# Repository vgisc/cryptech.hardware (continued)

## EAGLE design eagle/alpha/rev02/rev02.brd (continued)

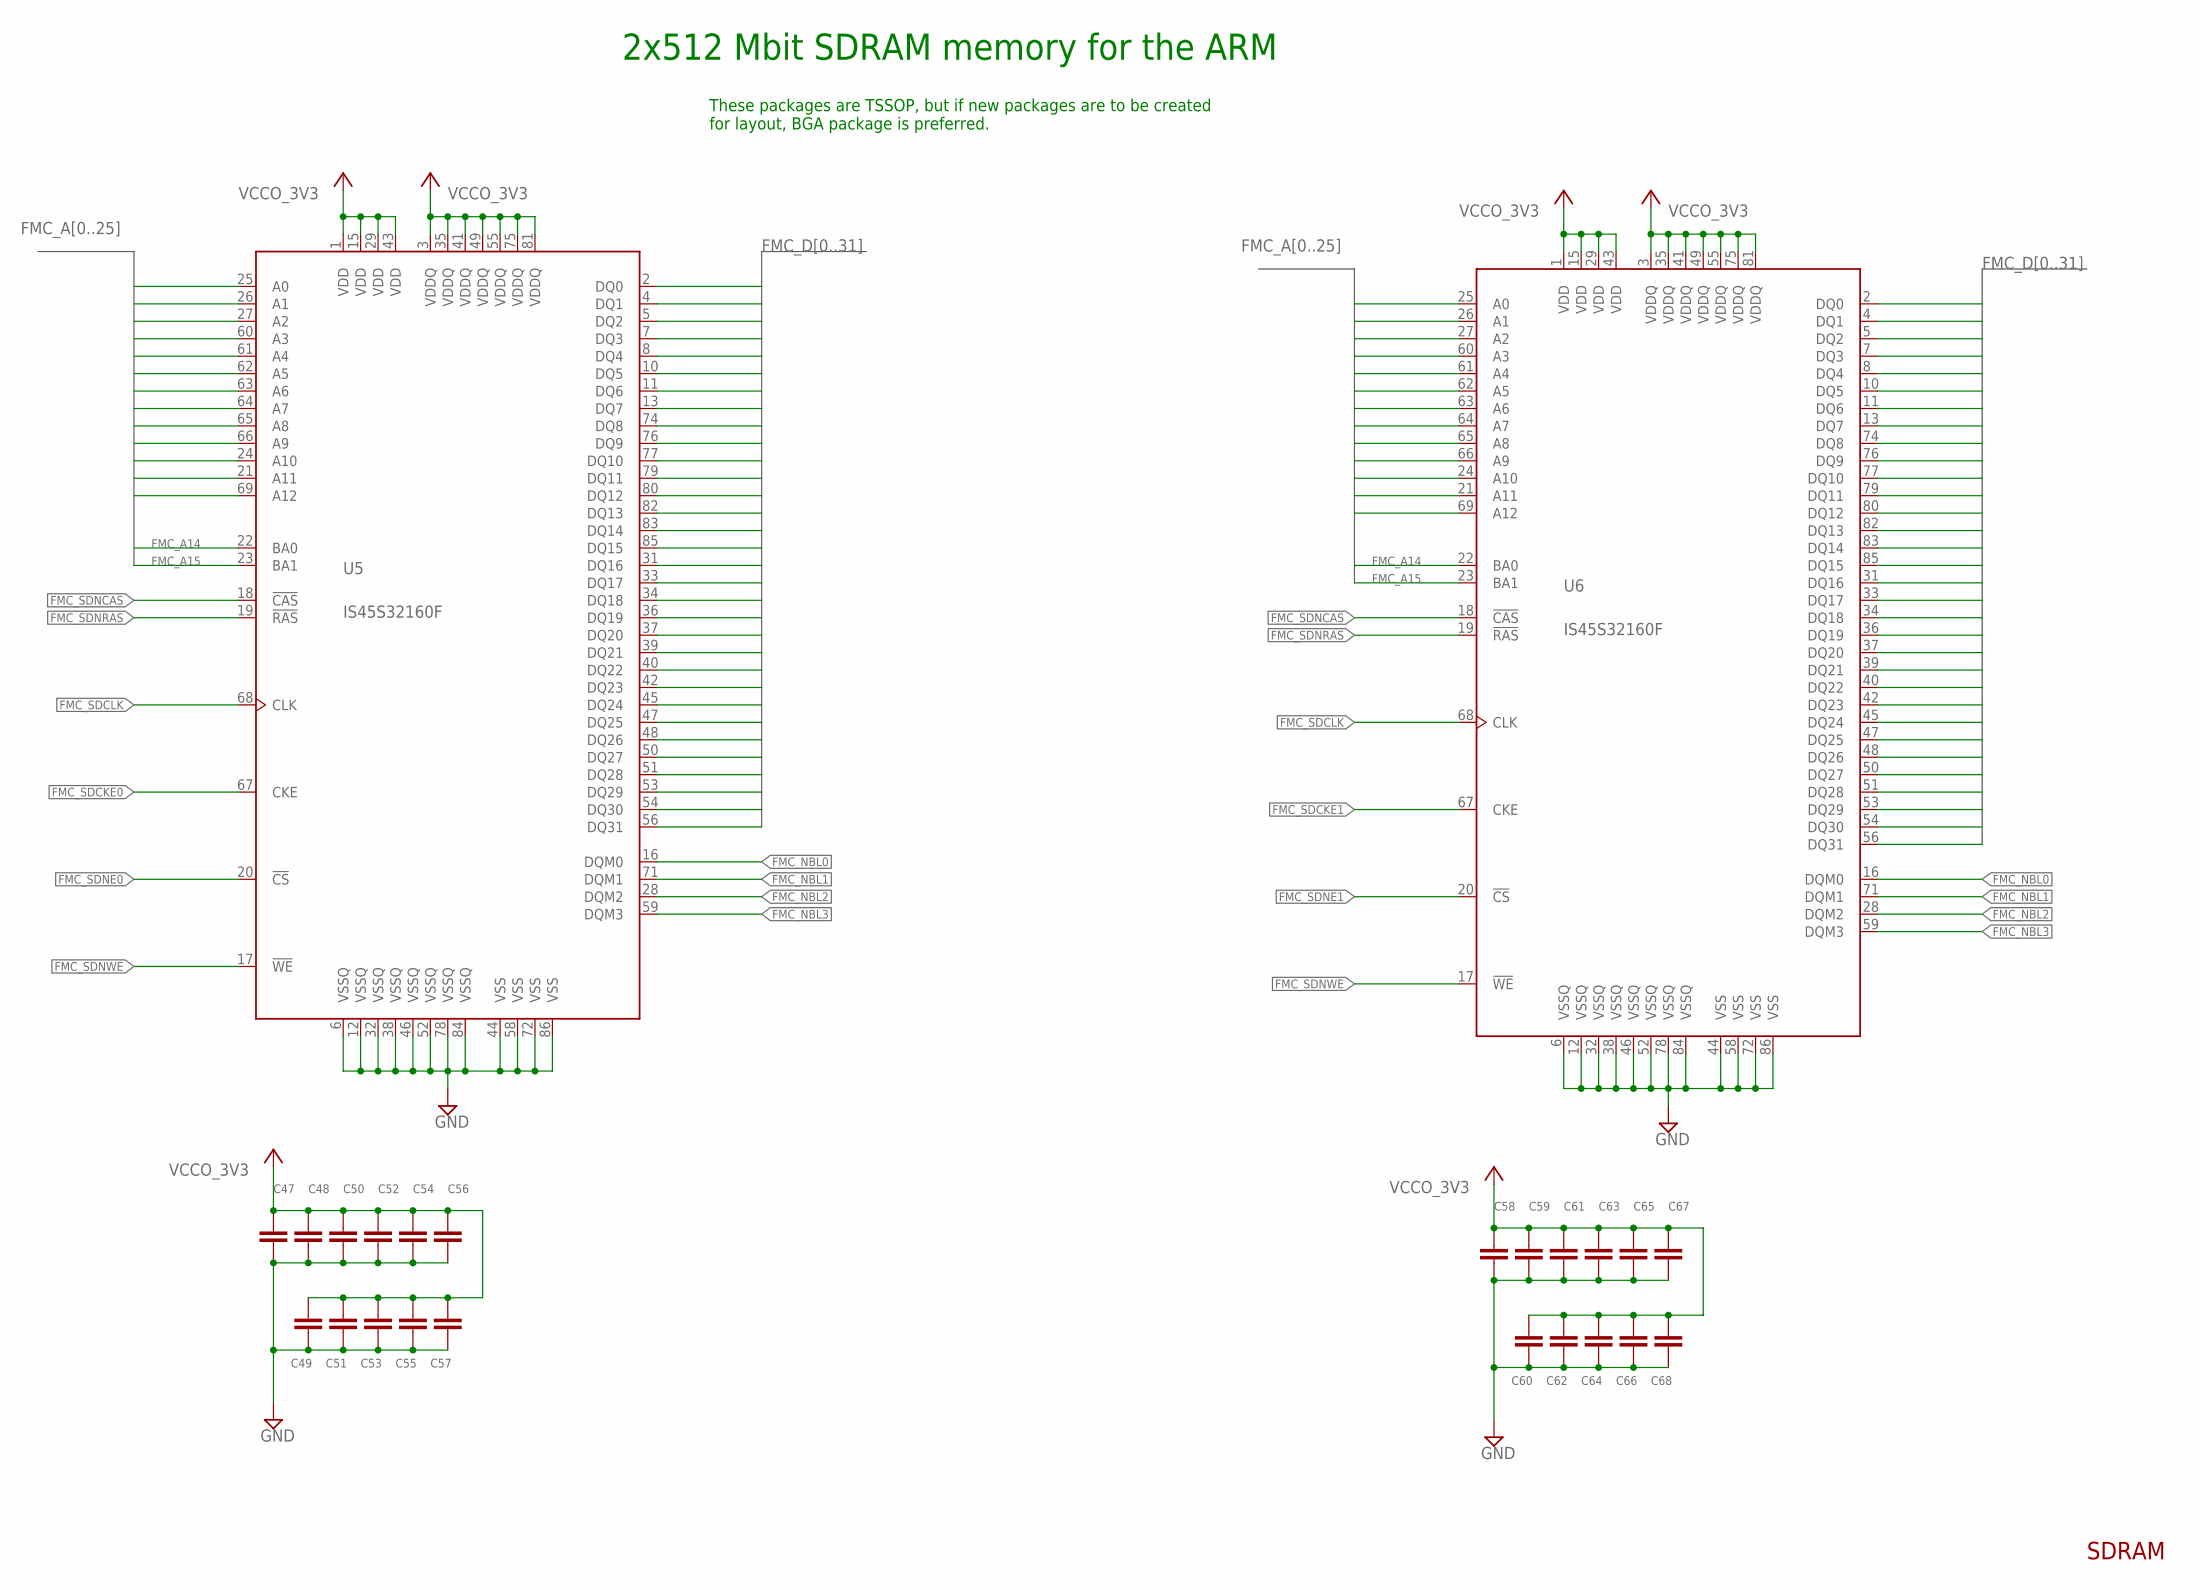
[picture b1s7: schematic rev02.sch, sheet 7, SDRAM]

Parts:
C47, C48, C49, C50, C51, C52, C53, C54, C55, C56, C57, C58, C59, C60, C61, C62, C63, C64, C65, C66, C67, C68: 0.1 uF; C0402
U5, U6: IS45S32160F; TSOP2-86L

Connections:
FMC_A0: U5.25 (A0), U6.25 (A0); also elsewhere on the board
FMC_A1: U5.26 (A1), U6.26 (A1); also elsewhere on the board
FMC_A2: U5.27 (A2), U6.27 (A2); also elsewhere on the board
FMC_A3: U5.60 (A3), U6.60 (A3); also elsewhere on the board
FMC_A4: U5.61 (A4), U6.61 (A4); also elsewhere on the board
FMC_A5: U5.62 (A5), U6.62 (A5); also elsewhere on the board
FMC_A6: U5.63 (A6), U6.63 (A6); also elsewhere on the board
FMC_A7: U5.64 (A7), U6.64 (A7); also elsewhere on the board
FMC_A8: U5.65 (A8), U6.65 (A8); also elsewhere on the board
FMC_A9: U5.66 (A9), U6.66 (A9); also elsewhere on the board
FMC_A10: U5.24 (A10), U6.24 (A10); also elsewhere on the board
FMC_A11: U5.21 (A11), U6.21 (A11); also elsewhere on the board
FMC_A12: U5.69 (A12), U6.69 (A12); also elsewhere on the board
FMC_A14: U5.22 (BA0), U6.22 (BA0); also elsewhere on the board
FMC_A15: U5.23 (BA1), U6.23 (BA1); also elsewhere on the board
FMC_D0: U5.2 (DQ0), U6.2 (DQ0); also elsewhere on the board
FMC_D1: U5.4 (DQ1), U6.4 (DQ1); also elsewhere on the board
FMC_D2: U5.5 (DQ2), U6.5 (DQ2); also elsewhere on the board
FMC_D3: U5.7 (DQ3), U6.7 (DQ3); also elsewhere on the board
FMC_D4: U5.8 (DQ4), U6.8 (DQ4); also elsewhere on the board
FMC_D5: U5.10 (DQ5), U6.10 (DQ5); also elsewhere on the board
FMC_D6: U5.11 (DQ6), U6.11 (DQ6); also elsewhere on the board
FMC_D7: U5.13 (DQ7), U6.13 (DQ7); also elsewhere on the board
FMC_D8: U5.74 (DQ8), U6.74 (DQ8); also elsewhere on the board
FMC_D10: U5.76 (DQ9), U5.77 (DQ10), U6.76 (DQ9), U6.77 (DQ10); also elsewhere on the board
FMC_D11: U5.79 (DQ11), U6.79 (DQ11); also elsewhere on the board
FMC_D12: U5.80 (DQ12), U6.80 (DQ12); also elsewhere on the board
FMC_D13: U5.82 (DQ13), U6.82 (DQ13); also elsewhere on the board
FMC_D14: U5.83 (DQ14), U6.83 (DQ14); also elsewhere on the board
FMC_D15: U5.85 (DQ15), U6.85 (DQ15); also elsewhere on the board
FMC_D16: U5.31 (DQ16), U6.31 (DQ16); also elsewhere on the board
FMC_D17: U5.33 (DQ17), U6.33 (DQ17); also elsewhere on the board
FMC_D18: U5.34 (DQ18), U6.34 (DQ18); also elsewhere on the board
FMC_D19: U5.36 (DQ19), U6.36 (DQ19); also elsewhere on the board
FMC_D20: U5.37 (DQ20), U6.37 (DQ20); also elsewhere on the board
FMC_D21: U5.39 (DQ21), U6.39 (DQ21); also elsewhere on the board
FMC_D22: U5.40 (DQ22), U6.40 (DQ22); also elsewhere on the board
FMC_D23: U5.42 (DQ23), U6.42 (DQ23); also elsewhere on the board
FMC_D24: U5.45 (DQ24), U6.45 (DQ24); also elsewhere on the board
FMC_D25: U5.47 (DQ25), U6.47 (DQ25); also elsewhere on the board
FMC_D26: U5.48 (DQ26), U6.48 (DQ26); also elsewhere on the board
FMC_D27: U5.50 (DQ27), U6.50 (DQ27); also elsewhere on the board
FMC_D28: U5.51 (DQ28), U6.51 (DQ28); also elsewhere on the board
FMC_D29: U5.53 (DQ29), U6.53 (DQ29); also elsewhere on the board
FMC_D30: U5.54 (DQ30), U6.54 (DQ30); also elsewhere on the board
FMC_D31: U5.56 (DQ31), U6.56 (DQ31); also elsewhere on the board
FMC_NBL0: U5.16 (DQM0), U6.16 (DQM0); also elsewhere on the board
FMC_NBL1: U5.71 (DQM1), U6.71 (DQM1); also elsewhere on the board
FMC_NBL2: U5.28 (DQM2), U6.28 (DQM2); also elsewhere on the board
FMC_NBL3: U5.59 (DQM3), U6.59 (DQM3); also elsewhere on the board
FMC_SDCKE0: U5.67 (CKE); also elsewhere on the board
FMC_SDCKE1: U6.67 (CKE); also elsewhere on the board
FMC_SDCLK: U5.68 (CLK), U6.68 (CLK); also elsewhere on the board
FMC_SDNCAS: U5.18 (!CAS), U6.18 (!CAS); also elsewhere on the board
FMC_SDNE0: U5.20 (!CS); also elsewhere on the board
FMC_SDNE1: U6.20 (!CS); also elsewhere on the board
FMC_SDNRAS: U5.19 (!RAS), U6.19 (!RAS); also elsewhere on the board
FMC_SDNWE: U5.17 (!WE), U6.17 (!WE); also elsewhere on the board
GND: C47.2, C48.2, C49.2, C50.2, C51.2, C52.2, C53.2, C54.2, C55.2, C56.2, C57.2, C58.2, C59.2, C60.2, C61.2, C62.2, C63.2, C64.2, C65.2, C66.2, C67.2, C68.2, U5.6 (VSSQ), U5.12 (VSSQ), U5.32 (VSSQ), U5.38 (VSSQ), U5.44 (VSS), U5.46 (VSSQ), U5.52 (VSSQ), U5.58 (VSS), U5.72 (VSS), U5.78 (VSSQ), U5.84 (VSSQ), U5.86 (VSS), U6.6 (VSSQ), U6.12 (VSSQ), U6.32 (VSSQ), U6.38 (VSSQ), U6.44 (VSS), U6.46 (VSSQ), U6.52 (VSSQ), U6.58 (VSS), U6.72 (VSS), U6.78 (VSSQ), U6.84 (VSSQ), U6.86 (VSS); also elsewhere on the board
VCCO_3V3: C47.1, C48.1, C49.1, C50.1, C51.1, C52.1, C53.1, C54.1, C55.1, C56.1, C57.1, C58.1, C59.1, C60.1, C61.1, C62.1, C63.1, C64.1, C65.1, C66.1, C67.1, C68.1, U5.1 (VDD), U5.3 (VDDQ), U5.15 (VDD), U5.29 (VDD), U5.35 (VDDQ), U5.41 (VDDQ), U5.43 (VDD), U5.49 (VDDQ), U5.55 (VDDQ), U5.75 (VDDQ), U5.81 (VDDQ), U6.1 (VDD), U6.3 (VDDQ), U6.15 (VDD), U6.29 (VDD), U6.35 (VDDQ), U6.41 (VDDQ), U6.43 (VDD), U6.49 (VDDQ), U6.55 (VDDQ), U6.75 (VDDQ), U6.81 (VDDQ); also elsewhere on the board

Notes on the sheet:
2x512 Mbit SDRAM memory for the ARM
SDRAM
These packages are TSSOP, but if new packages are to be created for layout, BGA package is preferred.

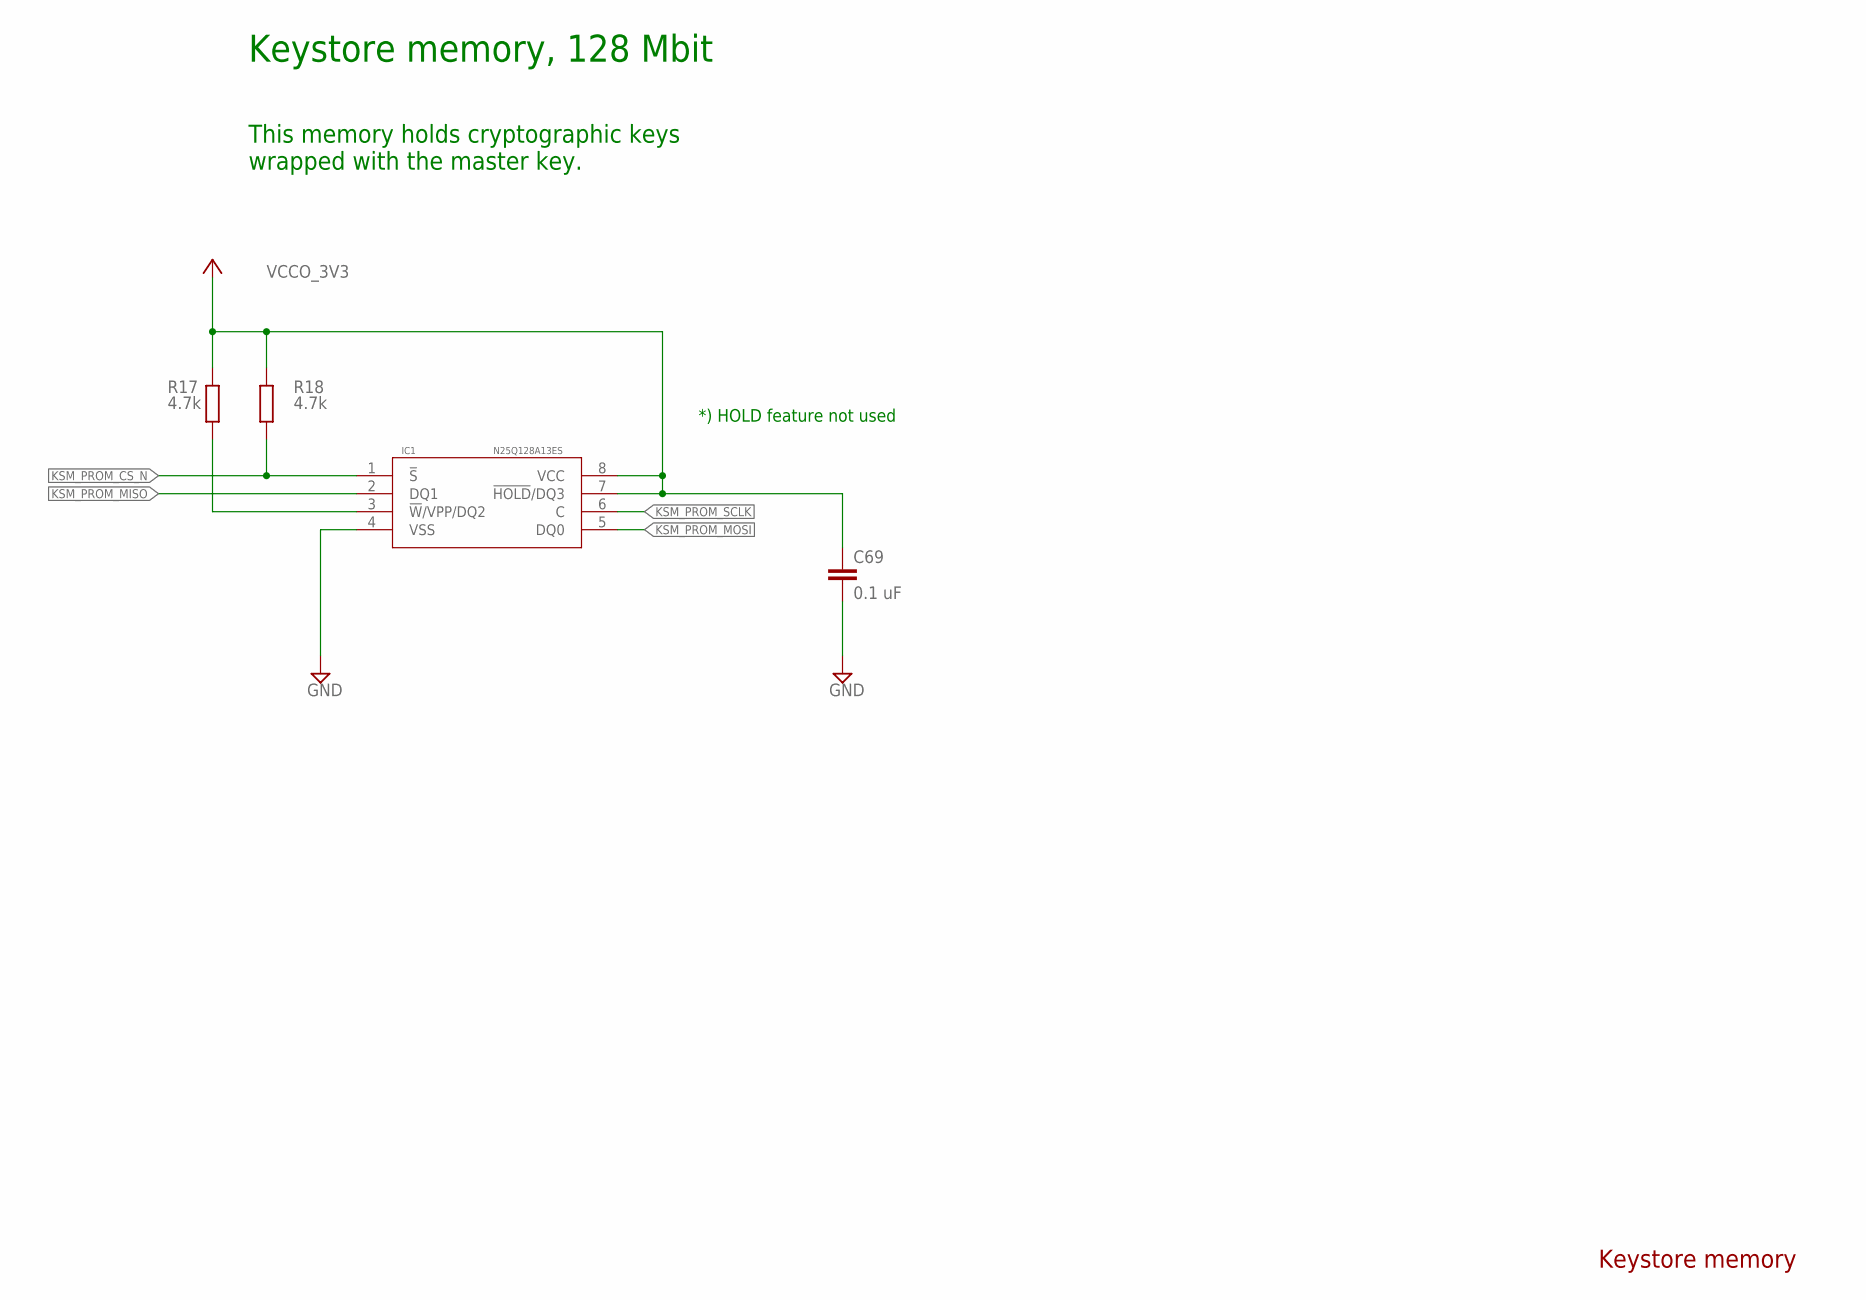
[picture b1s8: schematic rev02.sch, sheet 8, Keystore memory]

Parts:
C69: 0.1 uF; C0402; TOLERANCE 10%
IC1: N25Q128A13ES; SO08
R17, R18: 4.7k; R0402; TOLERANCE 5%

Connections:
GND: C69.2, IC1.4 (VSS); also elsewhere on the board
KSM_PROM_CS_N: IC1.1 (!S), R18.2; also elsewhere on the board
KSM_PROM_MISO: IC1.2 (DQ1); also elsewhere on the board
KSM_PROM_MOSI: IC1.5 (DQ0); also elsewhere on the board
KSM_PROM_SCLK: IC1.6 (C); also elsewhere on the board
unnamed: IC1.3 (!W!/VPP/DQ2), R17.2
VCCO_3V3: C69.1, IC1.7 (!HOLD!/DQ3), IC1.8 (VCC), R17.1, R18.1; also elsewhere on the board

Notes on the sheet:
*) HOLD feature not used
This memory holds cryptographic keys wrapped with the master key.
Keystore memory, 128 Mbit
Keystore memory

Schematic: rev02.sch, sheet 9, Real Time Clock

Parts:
C70, C71: 5 pF; C0402
R19, R20, R21: 10k; R0402; TOLERANCE 5%
U7: MCP79412-I/SN; SOIC127P600X175-8N
X1: XTAL-3.2X1.5; XTAL3215; MPN ABS07-32.768KHZ-T

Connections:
3V3_BATT: U7.3 (VBAT); also elsewhere on the board
GND: C70.1, C71.1, U7.4 (VSS); also elsewhere on the board
RTC_MFP: R21.2, U7.7 (MFP); also elsewhere on the board
RTC_SCL: R20.2, U7.6 (SCL); also elsewhere on the board
RTC_SDA: R19.2, U7.5 (SDA); also elsewhere on the board
RTC_X1: C70.2, U7.1 (X1), X1.P$1
RTC_X2: C71.2, U7.2 (X2), X1.P$2
VCC: R19.1, R20.1, R21.1; also elsewhere on the board
VCCO_3V3: U7.8 (VCC); also elsewhere on the board

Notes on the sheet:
CL 12.5 pF
MFP is Multi Function Pin. GPIO output from RTC.
i2c pull-ups, typically 10K for 100kHz
Real Time Clock

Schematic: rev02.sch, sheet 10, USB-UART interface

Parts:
C72, C82: 4.7 uF; C0603
C73, C74, C76, C79, C81, C83, C84, C85, C86, C214: 0.1 uF; C0402
C75, C78: 5 pF; C0402
C77, C80: 10 uF; C0805
CN1: HOST; USB-MINIB
FB1, FB2: 600R 500mA; _0603MP
IC5: RCLAMP0502ASC-89; RCLAMP0502A
J2: M03X2NO_SILK; 2X3-NS
LED5: YELLOW; CHIP-LED0603
LED6: GREEN; CHIP-LED0603
R22: 12k; R0402; TOLERANCE 1%
R23, R91: 10k; R0402; TOLERANCE 5%
R24, R25: 330; R0402; TOLERANCE 5%
R86, R87: 100; R0402; TOLERANCE 5%
U8: FT232H_SERIAL; FT2323HL_LQFP48
Y1: 12 MHz; CRYSTAL_3.2X2.5; TOLERANCE ±30 ppm; MPN ABM8G-12.000MHZ-4Y-T3

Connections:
FT_CTS: U8.16 (CTS#); also elsewhere on the board
FT_DTR: U8.17 (DTR#); also elsewhere on the board
FT_REF: R22.1, U8.5 (REF)
FT_RESET: R23.1, U8.34 (!RESET)
FT_RTS: U8.15 (RTS#); also elsewhere on the board
FT_RXD: R87.1; also elsewhere on the board
FT_RXD1: J2.5, R87.2, U8.14 (RXD)
FT_RXLED: R24.2, U8.27 (RXLED#)
FT_TXD: R86.1, R91.2; also elsewhere on the board
FT_TXD1: J2.6, R86.2, U8.13 (TXD)
FT_TXLED: R25.2, U8.28 (TXLED#)
FT_VCC3V3: C82.1, C83.1, C84.1, C85.1, C86.1, FB1.1, FB2.1, LED5.A, LED6.A, R23.2, U8.12 (VCCIO), U8.24 (VCCIO), U8.39 (VCCD), U8.46 (VCCIO)
FT_VCCA: C76.1, U8.37 (VCCA)
FT_VCCORE: C74.1, U8.38 (VCCORE)
FT_VPHY: C77.1, C79.1, FB1.2, U8.3 (VPHY)
FT_VPLL: C80.1, C81.1, FB2.2, U8.8 (VPLL)
FT_VREGIN: C72.1, C73.1, CN1.VBUS, IC5.5 (VCC), U8.40 (VREGIN)
GND: C72.2, C73.2, C74.2, C75.1, C76.2, C77.2, C78.1, C79.2, C80.2, C81.2, C82.2, C83.2, C84.2, C85.2, C86.2, C214.2, CN1.GND, IC5.2 (GND), J2.1, R22.2, U8.4 (AGND), U8.9 (AGND), U8.10 (GND), U8.11 (GND), U8.22 (GND), U8.23 (GND), U8.35 (GND), U8.36 (GND), U8.41 (AGND), U8.42 (TEST), U8.47 (GND), U8.48 (GND); also elsewhere on the board
unnamed: C75.2, U8.1 (XCSI), Y1.1
unnamed: C78.2, U8.2 (XCSO), Y1.2
unnamed: LED5.C, R24.1
unnamed: LED6.C, R25.1
unnamed: CN1.D+, IC5.6 (IN1)
unnamed: CN1.D-, IC5.4 (IN2)
USB_DM: IC5.3 (OUT2), U8.6 (DM)
USB_DP: IC5.1 (OUT1), U8.7 (DP)
VCCO_3V3: C214.1, J2.2, R91.1; also elsewhere on the board

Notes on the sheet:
DS_FT232H.pdf 6.1 USB Bus Powered Configuration copy of reference circuit
Place close to FT232
CL 10pF
Application access USB UART
USB-UART interface
If possible, line up with corresponding header for MGMT USB-UART and label pins on silk screen

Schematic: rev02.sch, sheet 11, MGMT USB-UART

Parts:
C87, C97: 4.7 uF; C0603
C88, C89, C91, C94, C96, C98, C99, C100, C101, C215: 0.1 uF; C0402
C90, C93: 5 pF; C0402
C92, C95: 10 uF; C0805
CN2: HOST; USB-MINIB
FB3, FB4: 600R 500mA; _0603MP
IC6: RCLAMP0502ASC-89; RCLAMP0502A
J3: M03X2NO_SILK; 2X3-NS
LED7: YELLOW; CHIP-LED0603
LED8: GREEN; CHIP-LED0603
R26: 12k; R0402; TOLERANCE 1%
R27, R90: 10k; R0402; TOLERANCE 5%
R28, R29: 330; R0402; TOLERANCE 5%
R88, R89: 100; R0402; TOLERANCE 5%
U9: FT232H_SERIAL; FT2323HL_LQFP48
Y2: 12 MHz; CRYSTAL_3.2X2.5; TOLERANCE ±30 ppm; MPN ABM8G-12.000MHZ-4Y-T3

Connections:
FT_MGMT_CTS: U9.16 (CTS#); also elsewhere on the board
FT_MGMT_DTR: U9.17 (DTR#); also elsewhere on the board
FT_MGMT_RTS: U9.15 (RTS#); also elsewhere on the board
FT_MGMT_RXD: R89.1; also elsewhere on the board
FT_MGMT_RXD1: J3.5, R89.2
FT_MGMT_TXD: R88.1, R90.2; also elsewhere on the board
FT_MGMT_TXD1: J3.6, R88.2
FT_MGMT_VCC3V3: C97.1, C98.1, C99.1, C100.1, C101.1, FB3.1, FB4.1, LED7.A, LED8.A, R27.2, U9.12 (VCCIO), U9.24 (VCCIO), U9.39 (VCCD), U9.46 (VCCIO)
FT_MGMT_VPHY: C92.1, C94.1, FB3.2, U9.3 (VPHY)
FT_MGMT_VPLL: C95.1, C96.1, FB4.2, U9.8 (VPLL)
FT_MGMT_VREGIN: C87.1, C88.1, CN2.VBUS, IC6.5 (VCC), U9.40 (VREGIN)
FT_REF1: R26.1, U9.5 (REF)
FT_RESET1: R27.1, U9.34 (!RESET)
FT_RXLED1: R28.2, U9.27 (RXLED#)
FT_TXLED1: R29.2, U9.28 (TXLED#)
FT_VCCA1: C91.1, U9.37 (VCCA)
FT_VCCORE1: C89.1, U9.38 (VCCORE)
GND: C87.2, C88.2, C89.2, C90.1, C91.2, C92.2, C93.1, C94.2, C95.2, C96.2, C97.2, C98.2, C99.2, C100.2, C101.2, C215.2, CN2.GND, IC6.2 (GND), J3.1, R26.2, U9.4 (AGND), U9.9 (AGND), U9.10 (GND), U9.11 (GND), U9.22 (GND), U9.23 (GND), U9.35 (GND), U9.36 (GND), U9.41 (AGND), U9.42 (TEST), U9.47 (GND), U9.48 (GND); also elsewhere on the board
unnamed: LED7.C, R28.1
unnamed: LED8.C, R29.1
unnamed: C93.2, U9.2 (XCSO), Y2.2
unnamed: C90.2, U9.1 (XCSI), Y2.1
unnamed: CN2.D+, IC6.6 (IN1)
unnamed: CN2.D-, IC6.4 (IN2)
USB_MGMT_DM: IC6.3 (OUT2), J3.4, U9.6 (DM)
USB_MGMT_DP: IC6.1 (OUT1), J3.3, U9.7 (DP)
VCCO_3V3: C215.1, J3.2, R90.1; also elsewhere on the board

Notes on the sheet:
DS_FT232H.pdf 6.1 USB Bus Powered Configuration copy of reference circuit
Place close to FT232
CL 10pF
Management access USB UART
MGMT USB-UART
If possible, line up with corresponding header for USB-UART and label pins on silk screen

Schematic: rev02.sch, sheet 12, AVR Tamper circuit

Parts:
C102: 10 uF; C0805
C103, C104, C105: 0.1 uF; C0402
JP3: AVR_SPI_PRG_62X3_LOCK; 2X3_LOCK
JP4: M03LOCK; 1X03_LOCK
JP5: M10LOCK; 1X10_LOCK
LED9: GREEN; CHIP-LED0603
LED10: RED; CHIP-LED0603
LED11: BLUE; CHIP-LED0603
LED12: YELLOW; CHIP-LED0603
R30, R82: 15k; R0402
R31: 330R; RESCAXE80P320X160X60-8N
S2: TACTILE_SWITCH
U10: ATTINY828R-AU; QFP80P900X900X120-32N

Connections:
3V3_BATT: C102.1, C103.1, C104.1, JP3.2, JP4.2, R30.2, R82.2, U10.4 (VCC), U10.18 (AVCC); also elsewhere on the board
AVR_GPIO_0: JP5.2, U10.31 (PC0_(PCINT16/ADC16/TOCC0/SS/XCK))
AVR_GPIO_1: JP5.3, U10.32 (PC1_(PCINT17/ADC17/TOCC1/INT0/CLKO))
AVR_GPIO_2: JP5.4, U10.1 ((PCINT18/ADC18/TOCC2/RXD/INT1)_PC2)
AVR_GPIO_3: JP5.5, U10.2 ((PCINT19/ADC19/TOCC3/TXD)_PC3)
AVR_GPIO_4: JP5.6, U10.3 ((PCINT20/ADC20/TOCC4)_PC4)
AVR_GPIO_5: JP5.7, U10.6 ((PCINT21/ADC21/TOCC5/ICP1/T0)_PC5)
AVR_GPIO_6: JP5.8, U10.7 ((PCINT22/ADC22/CLKI/TOCC6)_PC6)
AVR_GPIO_7: JP5.9, U10.8 ((PCINT23/ADC23/TOCC7/T1)_PC7)
AVR_GPIO_ARM_0: U10.17 (PB0_(PCINT8/ADC8)); also elsewhere on the board
AVR_GPIO_ARM_1: U10.19 (PB1_(PCINT9/ADC9)); also elsewhere on the board
AVR_GPIO_FPGA_2: U10.25 (PB6_(PCINT14/ADC14))
AVR_GPIO_FPGA_3: U10.26 (PB7_(PCINT15/ADC15))
AVR_LED1: R31.5, U10.9 ((PCINT0/ADC0)_PA0)
AVR_LED2: R31.6, U10.10 ((PCINT1/ADC1/AIN0)_PA1)
AVR_LED3: R31.7, U10.11 ((PCINT2/ADC2/AIN1)_PA2)
AVR_LED4: R31.8, U10.12 ((PCINT3/ADC3)_PA3)
AVR_PANIC: R82.1, S2.A2
AVR_RESET: JP3.5, R30.1, U10.29 (PD2_(!PCINT26/ADC26/RESET/DW))
GND: C102.2, C103.2, C104.2, C105.2, JP3.6, JP4.3, JP5.10, LED9.C, LED10.C, LED11.C, LED12.C, S2.B1, S2.B2, S2.G1, S2.G2, U10.5 (GND_2), U10.21 (GND); also elsewhere on the board
MKM_AVR_CS_N: U10.14 ((PC!INT5/ADC5)_PA5); also elsewhere on the board
MKM_AVR_MISO: JP3.1, U10.28 (PD1_(PCINT25/ADC25/MISO)); also elsewhere on the board
MKM_AVR_MOSI: JP3.4, U10.27 (PD0_(PCINT24/ADC24/SDA/MOSI)); also elsewhere on the board
MKM_AVR_SCK: JP3.3, U10.30 (PD3_(PCINT27/ADC27/SCL/SCK)); also elsewhere on the board
MKM_CONTROL_AVR_ENA: U10.15 ((PCINT6/ADC6)_PA6); also elsewhere on the board
unnamed: LED11.A, R31.4
unnamed: LED9.A, R31.3
unnamed: LED12.A, R31.2
unnamed: LED10.A, R31.1
VCC: C105.1, JP5.1; also elsewhere on the board
VCCO_3V3: JP4.1; also elsewhere on the board

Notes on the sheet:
AVR Tiny Tamper Detect MCU
Panic button
Expansion GPIO
Connector for external 3V3 battery. Place a jumper between pins 1-2 to "emulate" having a battery present.
AVR_GPIO* AVR_LED* and AVR_PANIC can be swapped.
AVR Tamper circuit

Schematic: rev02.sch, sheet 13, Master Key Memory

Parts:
C106, C107: 0.1 uF; C0402
IC4: 74AC244DW; SO20W
JP6: JP1Q; JP1
R33, R34: 4.7k; R0402
R79, R80, R81: 4.7k; R0402; TOLERANCE 5%
U12: 23K640-I/SN; SOIC127P600X175-8N

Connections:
3V3_BATT: C106.1, C107.1, IC4.20 (VCC), R33.1, R34.2, R79.2, R80.2, U12.8 (VCC); also elsewhere on the board
GND: C106.2, C107.2, IC4.10 (GND), JP6.1, R81.2, U12.4 (VSS); also elsewhere on the board
MKM_AVR_CS_N: IC4.2 (A1); also elsewhere on the board
MKM_AVR_MISO: IC4.12 (Y4), JP6.2; also elsewhere on the board
MKM_AVR_MOSI: IC4.6 (A3); also elsewhere on the board
MKM_AVR_SCK: IC4.4 (A2); also elsewhere on the board
MKM_CONTROL_AVR_ENA: IC4.1 (G), R80.1; also elsewhere on the board
MKM_CONTROL_FPGA_DIS: IC4.19 (G), R81.1
MKM_CS_N: IC4.9 (Y1), IC4.18 (Y1), R34.1, R79.1, U12.1 (!CS)
MKM_FPGA_CS_N: IC4.11 (A1); also elsewhere on the board
MKM_FPGA_MISO: IC4.3 (Y4); also elsewhere on the board
MKM_FPGA_MOSI: IC4.15 (A3); also elsewhere on the board
MKM_FPGA_SCK: IC4.13 (A2); also elsewhere on the board
MKM_MISO: IC4.8 (A4), IC4.17 (A4), U12.2 (SO)
MKM_MOSI: IC4.5 (Y3), IC4.14 (Y3), U12.5 (SI)
MKM_SCK: IC4.7 (Y2), IC4.16 (Y2), U12.6 (SCK)
unnamed: R33.2, U12.7 (!HOLD)

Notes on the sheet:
CS pull-up to disable MKM by default (allows programming of AVR)
Master Key Memory
SPI mux controlling access to the MKM. Normally, the FPGA has R/W access to the MKM but on a tamper event the tamper detect MCU (AVR) will grab access to the MKM and erase the contents.
Make AVR unable to read the MKM by installing this jumper
AVR access default disabled through pull-up
FPGA access default enabled through pull-down

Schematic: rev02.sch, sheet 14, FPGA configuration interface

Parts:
C108: 0.1 uF; C0402; TOLERANCE 10%
LED13: RED; CHIP-LED0603
Q4: 2N7002; SOT23
R35, R36, R37: 1.0k; R0402; TOLERANCE 5%
R38: 330; R0402; TOLERANCE 5%
R39: 100; R0402; TOLERANCE 5%
R40, R41, R42: 4.7k; R0402; TOLERANCE 5%
R43, R44, R45: 10k; R0402; TOLERANCE 5%
R62, R63, R71: 0; R0603; TOLERANCE 5%
SV1: MA08-1
U13: XC7A200TFBG484; FF484; MPN XC7A200T-1FBG484C

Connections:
FPGA_CFG_SCLK: R71.1; also elsewhere on the board
FPGA_CFG_SCLK1: R71.2, U13.L12 (CCLK_0)
FPGA_DONE: R39.1; also elsewhere on the board
FPGA_DONE_INT: LED13.C, R39.2, U13.G11 (DONE_0)
FPGA_INIT_B: Q4.1 (G), R42.2; also elsewhere on the board
FPGA_INIT_B_INT: Q4.3 (D), R40.1, R62.1
FPGA_INIT_B_INT1: R62.2, U13.U12 (INIT_B_0)
FPGA_JTAG_TCK: R45.1, SV1.2, U13.V12 (TCK_0)
FPGA_JTAG_TDI: R43.1, SV1.4, U13.R13 (TDI_0)
FPGA_JTAG_TDO: SV1.5, U13.U13 (TDO_0)
FPGA_JTAG_TMS: R44.1, SV1.3, U13.T13 (TMS_0)
FPGA_M0: R37.1, U13.U11 (M0_0)
FPGA_M1: R36.2, U13.U10 (M1_0)
FPGA_M2: R35.2, U13.U9 (M2_0)
FPGA_PROGRAM_B: R41.1, R63.1; also elsewhere on the board
FPGA_PROGRAM_B1: R63.2, U13.N12 (PROGRAM_B_0)
GND: C108.2, Q4.2 (S), R35.1, R36.1, R42.1, SV1.6, SV1.7, SV1.8, U13.E12 (VCCBATT_0); also elsewhere on the board
unnamed: LED13.A, R38.1
VCCO_3V3: C108.1, R37.2, R38.2, R40.2, R41.2, R43.2, R44.2, R45.2, SV1.1, U13.F12 (VCCO_0), U13.T12 (VCCO_0), U13.U8 (CFGBVS_0); also elsewhere on the board

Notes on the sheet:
*) Configuration Interface
M[2:0] == 3'b001 => Master SPI
*) Since VCCO is 3.3V, CFGBVS must be tied High. *) Battery is not used *) PROG_B is dedicated input -- can be driven by STM32 directly *) INIT_B is bi-directional open-drain, must be driven with MOSFET to ground
*) "Not DONE" LED, should be of red color
FPGA configuration interface

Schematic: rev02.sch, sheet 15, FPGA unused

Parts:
C109: 0.1 uF; C0402; TOLERANCE 10%
U13: XC7A200TFBG484; FF484; MPN XC7A200T-1FBG484C

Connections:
FPGA_VCCAUX_1V8: C109.1, U13.K10 (VCCADC_0); also elsewhere on the board
GND: C109.2, U13.K9 (GNDADC_0), U13.L9 (VREFN_0), U13.M10 (VREFP_0), U13.N9 (DXN_0), U13.N10 (DXP_0); also elsewhere on the board

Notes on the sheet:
*) Temperature Sensor [NOT USED]
*) XADC [NOT USED]
*) Transceivers [NOT USED]
FPGA unused

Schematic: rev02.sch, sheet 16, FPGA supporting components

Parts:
C110: 0.1 uF; C0402
C111: 0.01 uF; C0402; TOLERANCE 10%
C112: 0.1 uF; C0402; TOLERANCE 10%
IC2: 74AC244DW; SO20W
IC3: N25Q128A13ES; SO08
JP7, JP8, JP9: JP1Q; JP1
Q5: ASFL1; ASF; MPN ASFL1-50.000MHZ-EK-T
R4, R49: 0; R0402
R46, R47, R48, R50, R51: 4.7k; R0402; TOLERANCE 5%

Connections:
ARM_FPGA_CFG_CS_N: IC2.2 (A1); also elsewhere on the board
ARM_FPGA_CFG_MISO: IC2.12 (Y4); also elsewhere on the board
ARM_FPGA_CFG_MOSI: IC2.6 (A3); also elsewhere on the board
ARM_FPGA_CFG_SCLK: IC2.4 (A2); also elsewhere on the board
FPGA_CFG_CS_N: IC2.11 (A1); also elsewhere on the board
FPGA_CFG_CTRL_ARM_ENA: JP7.2; also elsewhere on the board
FPGA_CFG_CTRL_FPGA_DIS: JP8.2; also elsewhere on the board
FPGA_CFG_MISO: IC2.3 (Y4); also elsewhere on the board
FPGA_CFG_MOSI: IC2.15 (A3); also elsewhere on the board
FPGA_CFG_SCLK: IC2.13 (A2); also elsewhere on the board
FPGA_PROM_CS_N: IC2.9 (Y1), IC2.18 (Y1), IC3.1 (!S), R48.1, R51.1
FPGA_PROM_MISO: IC2.8 (A4), IC2.17 (A4), IC3.2 (DQ1)
FPGA_PROM_MOSI: IC2.5 (Y3), IC2.14 (Y3), IC3.5 (DQ0)
FPGA_PROM_SCLK: IC2.7 (Y2), IC2.16 (Y2), IC3.6 (C)
FPGA_PROM_W_N: IC3.3 (!W!/VPP/DQ2), JP9.1, R50.2
GND: C110.2, C111.2, C112.2, IC2.10 (GND), IC3.4 (VSS), Q5.2 (GND), R47.2, R50.1; also elsewhere on the board
unnamed: Q5.3 (FO), R4.2
unnamed: Q5.1 (OE), R49.1
SPI_A_TRISTATE: IC2.1 (G), JP7.1, R46.1
SPI_B_TRISTATE: IC2.19 (G), JP8.1, R47.1
VCCO_3V3: C110.1, C111.1, C112.1, IC2.20 (VCC), IC3.7 (!HOLD!/DQ3), IC3.8 (VCC), JP9.2, Q5.4 (VCC), R46.2, R48.2, R49.2, R51.2; also elsewhere on the board

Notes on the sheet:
*) HOLD feature not used *) PROM is write-protected by default, to disable write protection (such as during firmware update), jumper must be inserted
FPGA clock
FPGA config memory, 128 Mbit
SPI mux to let ARM override access to FPGA config memory (to reprogram FPGA)
Install this jumper to allow ARM to configure the FPGA
ARM access default disabled through pull-up
FPGA access default enabled through pull-down
FPGA supporting components

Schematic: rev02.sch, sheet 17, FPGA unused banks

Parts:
U13: XC7A200TFBG484; FF484; MPN XC7A200T-1FBG484C

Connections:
VCCO_3V3: U13.C1 (VCCO_35), U13.F2 (VCCO_35), U13.G19 (VCCO_15), U13.H6 (VCCO_35), U13.H16 (VCCO_15), U13.J3 (VCCO_35), U13.J13 (VCCO_15), U13.K20 (VCCO_15), U13.L17 (VCCO_15), U13.M4 (VCCO_35), U13.N1 (VCCO_35), U13.N21 (VCCO_15); also elsewhere on the board

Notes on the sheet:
*) Middle Right Bank
*) Upper Left Bank
*) Completely unused banks still must be powered
FPGA unused banks

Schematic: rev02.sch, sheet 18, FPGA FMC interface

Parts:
U13: XC7A200TFBG484; FF484; MPN XC7A200T-1FBG484C

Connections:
FMC_A0: U13.Y17 (IO_0_13); also elsewhere on the board
FMC_A1: U13.Y16 (IO_L1P_T0_13); also elsewhere on the board
FMC_A2: U13.AA16 (IO_L1N_T0_13); also elsewhere on the board
FMC_A3: U13.AB16 (IO_L2P_T0_13); also elsewhere on the board
FMC_A4: U13.AB17 (IO_L2N_T0_13); also elsewhere on the board
FMC_A5: U13.AA13 (IO_L3P_T0_DQS_13); also elsewhere on the board
FMC_A6: U13.AB13 (IO_L3N_T0_DQS_13); also elsewhere on the board
FMC_A7: U13.AA15 (IO_L4P_T0_13); also elsewhere on the board
FMC_A8: U13.AB15 (IO_L4N_T0_13); also elsewhere on the board
FMC_A9: U13.Y13 (IO_L5P_T0_13); also elsewhere on the board
FMC_A10: U13.AA14 (IO_L5N_T0_13); also elsewhere on the board
FMC_A11: U13.W14 (IO_L6P_T0_13); also elsewhere on the board
FMC_A12: U13.Y14 (IO_L6N_T0_VREF_13); also elsewhere on the board
FMC_A13: U13.AB11 (IO_L7P_T1_13); also elsewhere on the board
FMC_A14: U13.AB12 (IO_L7N_T1_13); also elsewhere on the board
FMC_A15: U13.AA9 (IO_L8P_T1_13); also elsewhere on the board
FMC_A16: U13.AB10 (IO_L8N_T1_13); also elsewhere on the board
FMC_A17: U13.AA10 (IO_L9P_T1_DQS_13); also elsewhere on the board
FMC_A18: U13.AA11 (IO_L9N_T1_DQS_13); also elsewhere on the board
FMC_A19: U13.V10 (IO_L10P_T1_13); also elsewhere on the board
FMC_A20: U13.W10 (IO_L10N_T1_13); also elsewhere on the board
FMC_A21: U13.Y11 (IO_L11P_T1_SRCC_13); also elsewhere on the board
FMC_A22: U13.Y12 (IO_L11N_T1_SRCC_13); also elsewhere on the board
FMC_A23: U13.W12 (IO_L12N_T1_MRCC_13); also elsewhere on the board
FMC_A24: U13.V13 (IO_L13P_T2_MRCC_13); also elsewhere on the board
FMC_A25: U13.V14 (IO_L13N_T2_MRCC_13); also elsewhere on the board
FMC_CLK: U13.W11 (IO_L12P_T1_MRCC_13); also elsewhere on the board
FMC_D0: U13.T3 (IO_0_34); also elsewhere on the board
FMC_D1: U13.T1 (IO_L1P_T0_34); also elsewhere on the board
FMC_D2: U13.U1 (IO_L1N_T0_34); also elsewhere on the board
FMC_D3: U13.U2 (IO_L2P_T0_34); also elsewhere on the board
FMC_D4: U13.V2 (IO_L2N_T0_34); also elsewhere on the board
FMC_D5: U13.R3 (IO_L3P_T0_DQS_34); also elsewhere on the board
FMC_D6: U13.R2 (IO_L3N_T0_DQS_34); also elsewhere on the board
FMC_D7: U13.W2 (IO_L4P_T0_34); also elsewhere on the board
FMC_D8: U13.Y2 (IO_L4N_T0_34); also elsewhere on the board
FMC_D9: U13.W1 (IO_L5P_T0_34); also elsewhere on the board
FMC_D10: U13.Y1 (IO_L5N_T0_34); also elsewhere on the board
FMC_D11: U13.U3 (IO_L6P_T0_34); also elsewhere on the board
FMC_D12: U13.V3 (IO_L6N_T0_VREF_34); also elsewhere on the board
FMC_D13: U13.AA1 (IO_L7P_T1_34); also elsewhere on the board
FMC_D14: U13.AB1 (IO_L7N_T1_34); also elsewhere on the board
FMC_D15: U13.AB3 (IO_L8P_T1_34); also elsewhere on the board
FMC_D16: U13.AB2 (IO_L8N_T1_34); also elsewhere on the board
FMC_D17: U13.Y3 (IO_L9P_T1_DQS_34); also elsewhere on the board
FMC_D18: U13.AA3 (IO_L9N_T1_DQS_34); also elsewhere on the board
FMC_D19: U13.AA5 (IO_L10P_T1_34); also elsewhere on the board
FMC_D20: U13.AB5 (IO_L10N_T1_34); also elsewhere on the board
FMC_D21: U13.Y4 (IO_L11P_T1_SRCC_34); also elsewhere on the board
FMC_D22: U13.AA4 (IO_L11N_T1_SRCC_34); also elsewhere on the board
FMC_D23: U13.V4 (IO_L12P_T1_MRCC_34); also elsewhere on the board
FMC_D24: U13.W4 (IO_L12N_T1_MRCC_34); also elsewhere on the board
FMC_D25: U13.R4 (IO_L13P_T2_MRCC_34); also elsewhere on the board
FMC_D26: U13.T4 (IO_L13N_T2_MRCC_34); also elsewhere on the board
FMC_D27: U13.T5 (IO_L14P_T2_SRCC_34); also elsewhere on the board
FMC_D28: U13.U5 (IO_L14N_T2_SRCC_34); also elsewhere on the board
FMC_D29: U13.W6 (IO_L15P_T2_DQS_34); also elsewhere on the board
FMC_D30: U13.W5 (IO_L15N_T2_DQS_34); also elsewhere on the board
FMC_D31: U13.U6 (IO_L16P_T2_34); also elsewhere on the board
FMC_NE1: U13.V5 (IO_L16N_T2_34); also elsewhere on the board
FMC_NL: U13.R6 (IO_L17P_T2_34); also elsewhere on the board
FMC_NOE: U13.T6 (IO_L17N_T2_34); also elsewhere on the board
FMC_NWAIT: U13.Y6 (IO_L18P_T2_34); also elsewhere on the board
FMC_NWE: U13.AA6 (IO_L18N_T2_34); also elsewhere on the board
VCCO_3V3: U13.AA7 (VCCO_34), U13.AA17 (VCCO_13), U13.AB4 (VCCO_34), U13.AB14 (VCCO_13), U13.R5 (VCCO_34), U13.T2 (VCCO_34), U13.V6 (VCCO_34), U13.V16 (VCCO_13), U13.W3 (VCCO_34), U13.W13 (VCCO_13), U13.Y10 (VCCO_13); also elsewhere on the board

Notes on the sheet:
*) Bottom Bank
*) Lower Left Bank
<-- FMC_A[...] signals can be swapped
<-- FMC_CLK signal _MUST_ go into either W11 or V13 (i.e. into one of the two positive (master) sides of the two available MRCC differential pairs)
<-- FMC_D[...] signals can be swapped
<-- FMC_* control signals can be swapped
FPGA FMC interface

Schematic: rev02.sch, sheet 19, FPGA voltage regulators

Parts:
C113, C114: 22 uF; C1210; TOLERANCE 20%
C115, C116: 0.047 uF; C0402; TOLERANCE 10%
C117, C118: 27pF; C0402; TOLERANCE 5%
C119, C120: 47 uF; C1210; TOLERANCE 20%
FB5, FB6: 0; 1206
R52, R54: 4.7k; R0402; TOLERANCE 5%
R53, R55: 62k; R0402; TOLERANCE 5%
R56, R58: 205k; R0402; TOLERANCE 1%
R57: 147k; R0402; TOLERANCE 1%
R59: 59k; R0402; TOLERANCE 1%
R60, R61: 470; R0402; TOLERANCE 5%
U14, U15: EN6347QI; QFN38_4X7X1.85

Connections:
FPGA_VCCAUX_1V8: FB5.2; also elsewhere on the board
GND: C113.2, C114.2, C115.2, C116.2, C119.2, C120.2, R53.1, R55.1, R57.1, R59.1, R60.1, R61.1, U14.13 (PGND), U14.14 (PGND), U14.15 (PGND), U14.16 (PGND), U14.17 (PGND), U14.18 (PGND), U14.32 (AGND), U14.P$39 (PGND), U14.P$40 (PGND), U15.13 (PGND), U15.14 (PGND), U15.15 (PGND), U15.16 (PGND), U15.17 (PGND), U15.18 (PGND), U15.32 (AGND), U15.P$39 (PGND), U15.P$40 (PGND); also elsewhere on the board
unnamed: C115.1, U14.30 (SS)
unnamed: R53.2, U14.29 (RLLM)
unnamed: R52.1, U14.26 (LLM/SYNC)
unnamed: C117.1, C119.1, FB5.1, R56.2, R60.2, U14.5 (VOUT), U14.6 (VOUT), U14.7 (VOUT), U14.8 (VOUT), U14.9 (VOUT), U14.10 (VOUT), U14.11 (VOUT)
unnamed: C117.2, R56.1, R57.2, U14.31 (VFB)
unnamed: C116.1, U15.30 (SS)
unnamed: R55.2, U15.29 (RLLM)
unnamed: R54.1, U15.26 (LLM/SYNC)
unnamed: C118.1, C120.1, FB6.1, R58.2, R61.2, U15.5 (VOUT), U15.6 (VOUT), U15.7 (VOUT), U15.8 (VOUT), U15.9 (VOUT), U15.10 (VOUT), U15.11 (VOUT)
unnamed: C118.2, R58.1, R59.2, U15.31 (VFB)
POK_VCCAUX: U14.28 (POK); also elsewhere on the board
POK_VCCO: U15.28 (POK); also elsewhere on the board
PWR_ENA_VCCAUX: U14.27 (ENABLE); also elsewhere on the board
PWR_ENA_VCCO: U15.27 (ENABLE); also elsewhere on the board
VCCO_3V3: FB6.2; also elsewhere on the board
VCC_5V0: C113.1, C114.1, R52.2, R54.2, U14.19 (PVIN), U14.20 (PVIN), U14.21 (PVIN), U14.33 (AVIN), U15.19 (PVIN), U15.20 (PVIN), U15.21 (PVIN), U15.33 (AVIN); also elsewhere on the board

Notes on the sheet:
*) FPGA Power Subsystem -- AUX and I/O
*) VCCAUX = 0.75V x (1 + 205 / 147) = 1.796V *) VCCO = 0.75V x (1 + 205 / 59) = 3.356 *) Minimal load current is 2 mA: 1.8V / 470 Ohm = ~4mA 3.3V / 470 Ohm = ~7mA *) Light-load mode is enabled
This is the 3V3 rail that powers both the FPGA and the ARM as well as various other components.
FPGA voltage regulators

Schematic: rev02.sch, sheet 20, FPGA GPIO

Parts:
C121, C122: 0.1 uF; C0402; TOLERANCE 10%
LED14: RED; CHIP-LED0603
LED15: GREEN; CHIP-LED0603
LED16: YELLOW; CHIP-LED0603
LED17: BLUE; CHIP-LED0603
R64: 330R; RESCAXE80P320X160X60-8N
SV2, SV3: MA08-2
U13: XC7A200TFBG484; FF484; MPN XC7A200T-1FBG484C

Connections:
FPGA_ENTROPY_DISABLE: U13.B18 (IO_L11N_T1_SRCC_16); also elsewhere on the board
FPGA_GCLK: U13.D17 (IO_L12P_T1_MRCC_16)
FPGA_GPIO_A_0: SV2.7, U13.C15 (IO_L3N_T0_DQS_16)
FPGA_GPIO_A_1: SV2.8, U13.E13 (IO_L4P_T0_16)
FPGA_GPIO_A_2: SV2.9, U13.E14 (IO_L4N_T0_16)
FPGA_GPIO_A_3: SV2.10, U13.E16 (IO_L5P_T0_16)
FPGA_GPIO_A_4: SV2.13, U13.D16 (IO_L5N_T0_16)
FPGA_GPIO_A_5: SV2.14, U13.D14 (IO_L6P_T0_16)
FPGA_GPIO_A_6: SV2.15, U13.D15 (IO_L6N_T0_VREF_16)
FPGA_GPIO_A_7: SV2.16, U13.B15 (IO_L7P_T1_16)
FPGA_GPIO_B_0: SV3.7, U13.B16 (IO_L7N_T1_16)
FPGA_GPIO_B_1: SV3.8, U13.C13 (IO_L8P_T1_16)
FPGA_GPIO_B_2: SV3.9, U13.B13 (IO_L8N_T1_16)
FPGA_GPIO_B_3: SV3.10, U13.A15 (IO_L9P_T1_DQS_16)
FPGA_GPIO_B_4: SV3.13, U13.A16 (IO_L9N_T1_DQS_16)
FPGA_GPIO_B_5: SV3.14, U13.A13 (IO_L10P_T1_16)
FPGA_GPIO_B_6: SV3.15, U13.A14 (IO_L10N_T1_16)
FPGA_GPIO_B_7: SV3.16, U13.B17 (IO_L11P_T1_SRCC_16)
FPGA_GPIO_LED_0: R64.4; also elsewhere on the board
FPGA_GPIO_LED_1: R64.3; also elsewhere on the board
FPGA_GPIO_LED_2: R64.2; also elsewhere on the board
FPGA_GPIO_LED_3: R64.1; also elsewhere on the board
FPGA_IRQ_N_0: U13.F14 (IO_L1N_T0_16); also elsewhere on the board
FPGA_IRQ_N_1: U13.F16 (IO_L2P_T0_16); also elsewhere on the board
FPGA_IRQ_N_2: U13.E17 (IO_L2N_T0_16); also elsewhere on the board
FPGA_IRQ_N_3: U13.C14 (IO_L3P_T0_DQS_16); also elsewhere on the board
GND: C121.2, C122.2, LED14.C, LED15.C, LED16.C, LED17.C, SV2.5, SV2.6, SV2.11, SV2.12, SV3.5, SV3.6, SV3.11, SV3.12; also elsewhere on the board
unnamed: LED17.A, R64.5
unnamed: LED15.A, R64.6
unnamed: LED16.A, R64.7
unnamed: LED14.A, R64.8
VCCO_3V3: C121.1, C122.1, SV2.1, SV2.2, SV2.3, SV2.4, SV3.1, SV3.2, SV3.3, SV3.4, U13.A17 (VCCO_16), U13.B14 (VCCO_16), U13.C21 (VCCO_16), U13.D18 (VCCO_16), U13.E15 (VCCO_16), U13.F22 (VCCO_16); also elsewhere on the board

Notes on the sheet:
*) Upper Right Bank
*) FPGA_GCLK signal _MUST_ go into either D17 or C18 (i.e. into one of the two positive (master) sides of the two available MRCC differential pairs)
*) FPGA_GPIO_* and FPGA_IRQ_N_* signals can be swapped
*) Signals, that are allowed to be swapped, can be be swapped with each other and/or moved to different pins within their bank.
NOTE: One of the FPGA_GPIO_* pins should be connected to one of the MRCC pins. The non-MRCC GPIO signals should be length matched to within 500 ps of the MRCC signal.
FPGA GPIO
